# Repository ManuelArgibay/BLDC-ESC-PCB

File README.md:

# Controlador de motor BLDC (ESC sensorless) — PCB en KiCad

Placa de potencia y acondicionamiento para controlar un motor BLDC trifásico sin sensores Hall desde una LaunchPad **TI Tiva C TM4C123GXL**. Integra el inversor trifásico con sus drivers, la detección de cruces por cero de la fuerza contraelectromotriz (BEMF) para conmutación sensorless y la alimentación de toda la placa a partir de una única entrada de 12 V.

Proyecto de la asignatura *Laboratori de Sistemes Electrònics I* (Grado en Ingeniería Electrónica de Telecomunicación, Universitat de Barcelona).

## Características

| | |
|---|---|
| Herramienta | KiCad 9 |
| Dimensiones | 70 × 90 mm, 2 taladros M3 |
| Capas | 4 (F.Cu, In1.Cu, In2.Cu, B.Cu), 1,57 mm |
| Alimentación | 12 V (bus del motor y lógica) |
| Etapa de potencia | 6 × MOSFET canal N en DPAK (TO-252), tres semipuentes |
| Drivers | 3 × IR2301 (high/low side con bootstrap) |
| Detección BEMF | LM339 (comparador cuádruple) + neutro virtual resistivo |
| Reguladores | AP1509-50 (buck 12 V → 5 V) + LMS8117 (LDO 5 V → 3,3 V) |
| Controlador | Tiva C TM4C123GXL (se monta sobre los conectores J1–J4) |

## Descripción del circuito

El esquema es jerárquico. La hoja raíz agrupa cuatro bloques: **TM4C123GXL** (conectores de la LaunchPad), **Motor** (que contiene las subhojas *Drivers* y *Comparadores*), **IO** (alimentación, conectores y LEDs) y **Testpoints**.

**Etapa de potencia (`Drivers.kicad_sch`).** Cada fase es un semipuente de dos NMOS (MxH/MxL) alimentado desde el bus de 12 V. Un IR2301 por fase genera las tensiones de puerta: el lado alto se alimenta por bootstrap (diodo 1N4149 + condensador entre VB y la fase), cada puerta tiene su resistencia serie (RGxH/RGxL) y cada entrada lógica una resistencia (RIxH/RIxL) desde la Tiva. Las entradas de lado alto van a pines con salida PWM y las de lado bajo a GPIO.

**Detección de BEMF (`Comparadores.kicad_sch`).** Tres resistencias en estrella (RFA/RFB/RFC) reconstruyen el neutro virtual del motor. La tensión de cada fase y la del neutro pasan por divisores resistivos que las llevan a un rango compatible con la lógica de 3,3 V, y un LM339 compara cada fase flotante contra el neutro. Las salidas en colector abierto tienen pull-up a 3,3 V y entran a la Tiva como señales digitales de cruce por cero, que el firmware usa para temporizar la conmutación.

**Alimentación e IO (`IO.kicad_sch`).** La entrada de 12 V (bornera) alimenta directamente el bus de potencia y los drivers. Un buck AP1509-50 (bobina de 47 µH, diodo Schottky B220) genera 5 V y un LDO LMS8117 baja a 3,3 V. Dos jumpers permiten elegir de dónde sale el raíl de 3,3 V de la placa: del LDO (`FUENTE`) y/o del regulador de la propia Tiva (`TIVA`). Hay un LED indicador de 12 V y otro del 3,3 V de la Tiva, y una bornera de tres vías para las fases del motor.

**Test points (`Testpoints.kicad_sch`).** Acceso a las entradas lógicas de los drivers, las puertas de los seis MOSFET, los nodos de bootstrap, las tres fases, VCC, 3,3 V y el potenciómetro, pensado para depurar la placa con osciloscopio.

## Asignación de pines (TM4C123GXL)

| Señal | Pin Tiva | Función |
|---|---|---|
| Fase A alto / bajo | PB5 / PD0 | Entradas HIN / LIN del IR2301 A |
| Fase B alto / bajo | PD1 / PB3 | Entradas HIN / LIN del IR2301 B |
| Fase C alto / bajo | PB7 / PF2 | Entradas HIN / LIN del IR2301 C |
| BEMF A / B / C | PD2 / PD3 / PD6 | Salidas del LM339 |
| Potenciómetro | PE0 (AIN3) | Consigna analógica de velocidad |
| SPI | PA2 (SCLK), PA5 (MOSI), PA4 (MISO), PF1 (SS) | Conector de expansión |

## Estructura del repositorio

```
Control Motor BLDC.kicad_pro   Proyecto de KiCad
Control Motor BLDC.kicad_sch   Hoja raíz del esquema
Control Motor BLDC.kicad_pcb   Layout
*.kicad_sch                    Subhojas (Drivers, Comparadores, IO, Motor, TM4C123GXL, Testpoints)
Footprints/                    Símbolos y footprints propios (NMOS DPAK, AP1509, LDO)
LSE-BLDC_control/              Firmware para la Tiva (Code Composer Studio, C bare-metal)
docs/                          Imágenes del README
```

Las librerías propias se referencian con `${KIPRJMOD}` en `fp-lib-table` y `sym-lib-table`, así que el proyecto abre sin configuración adicional en KiCad 9 o posterior.

## Autor

Manuel Argibay Molina y Max Pérez Piqué — [@ManuelArgibay](https://github.com/ManuelArgibay)

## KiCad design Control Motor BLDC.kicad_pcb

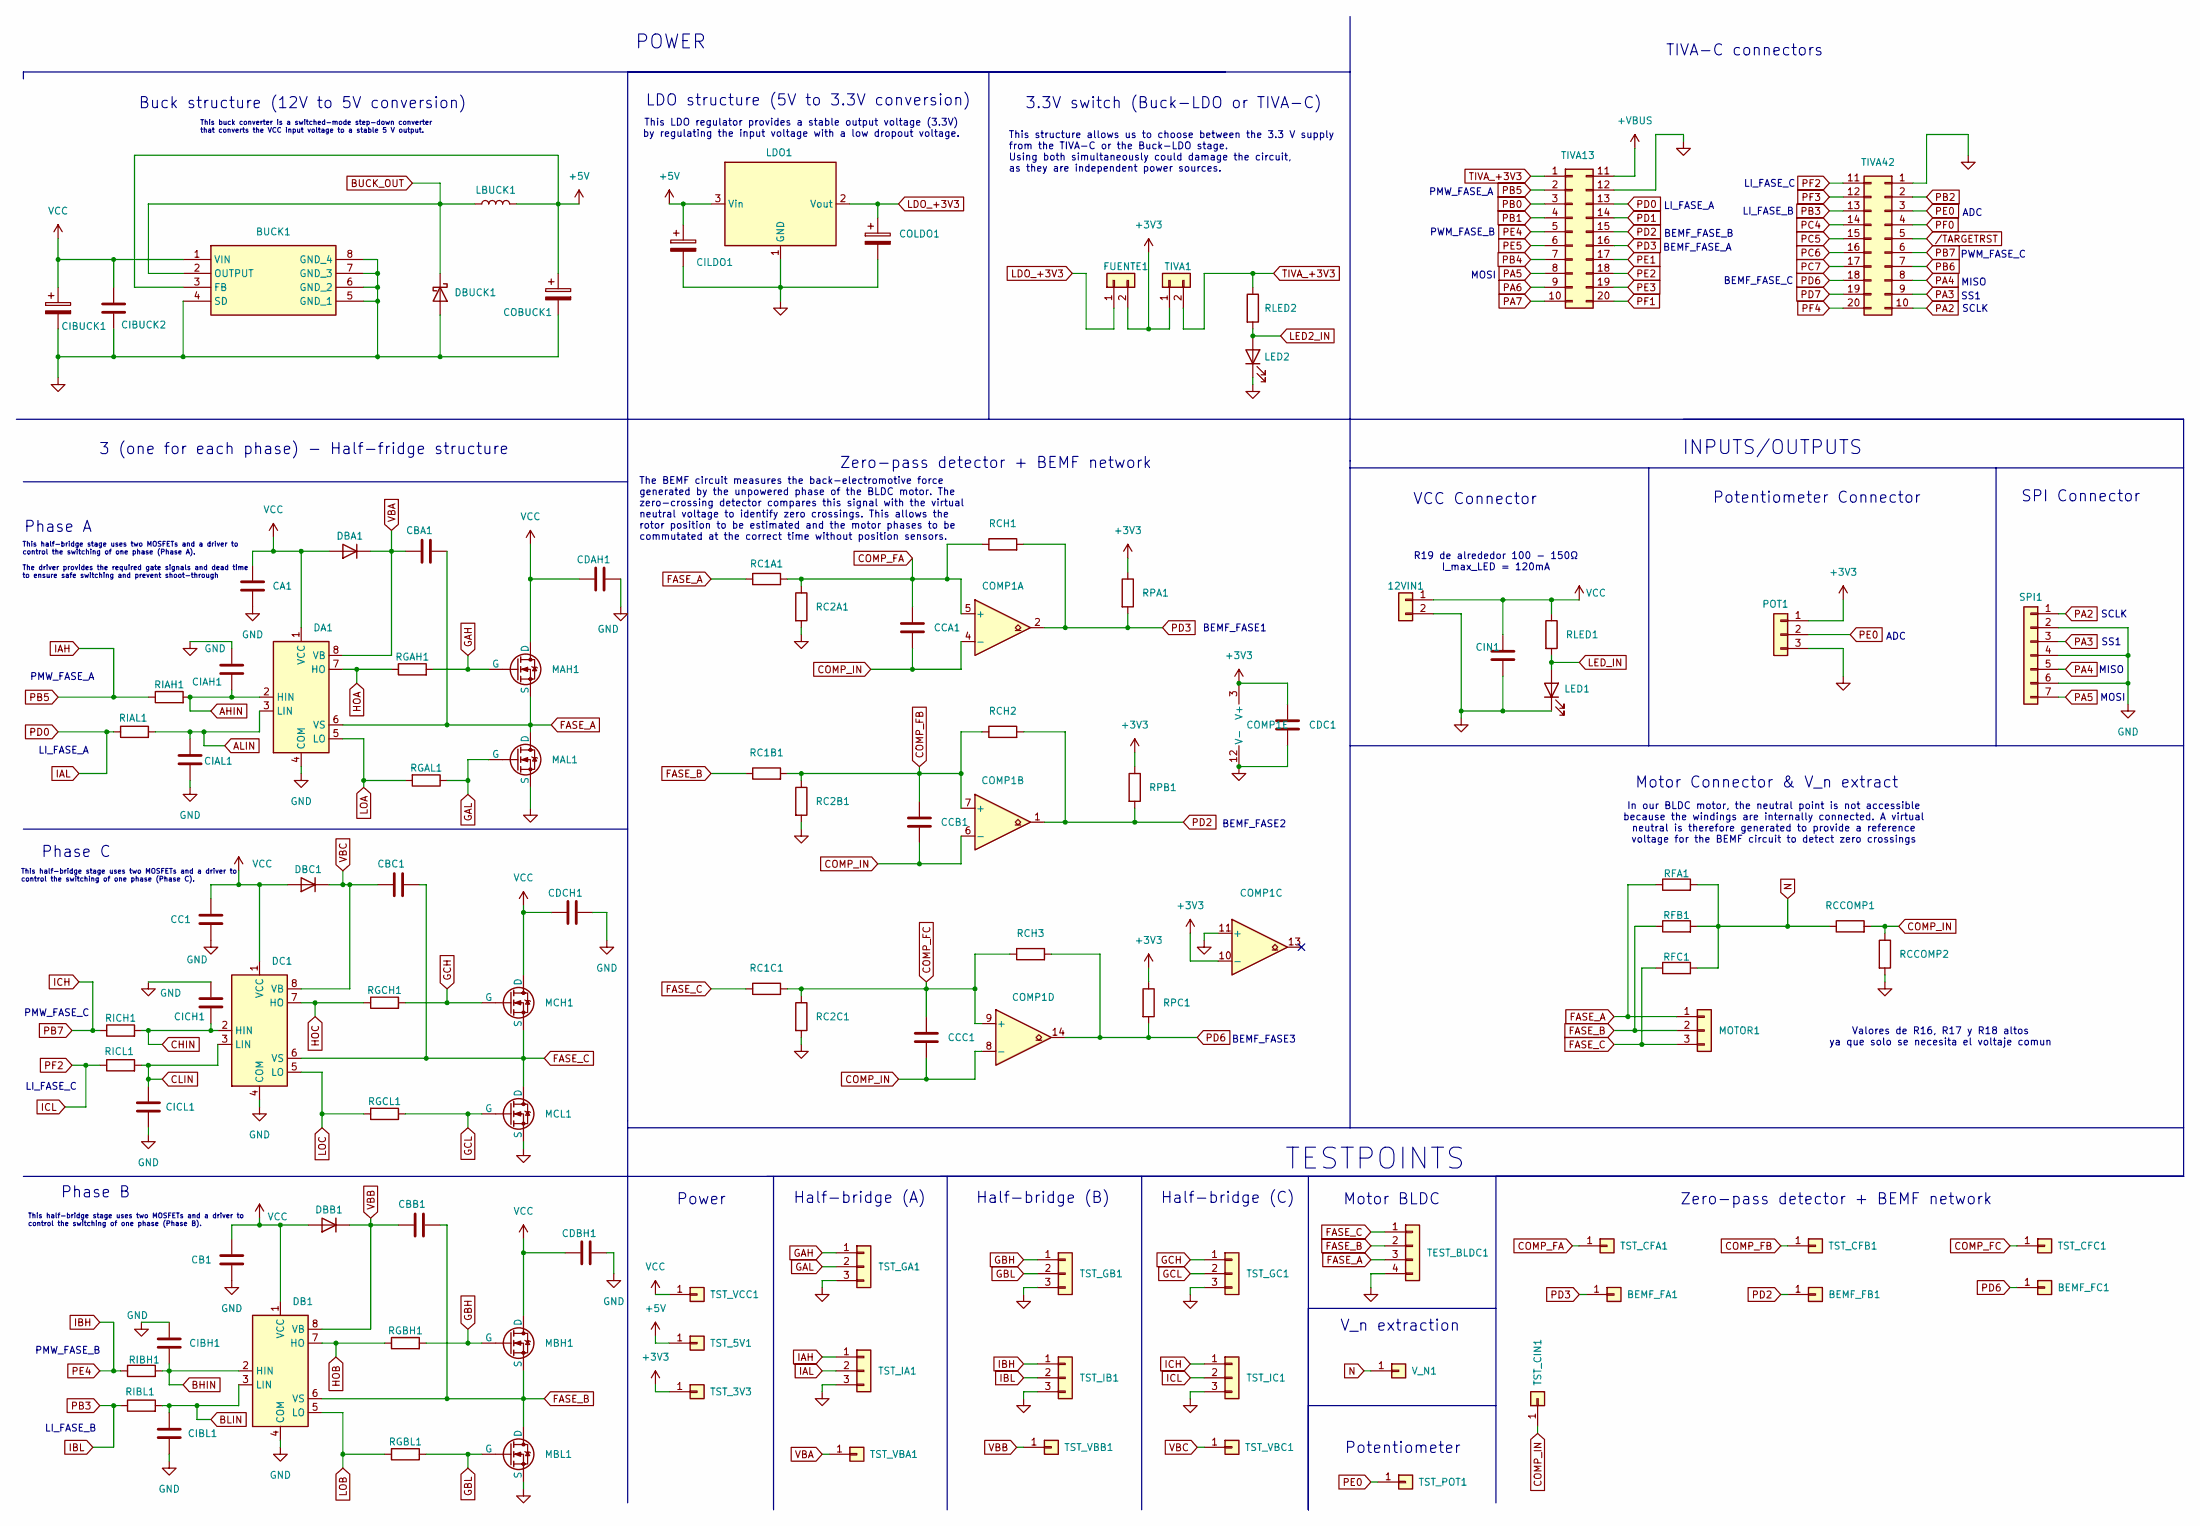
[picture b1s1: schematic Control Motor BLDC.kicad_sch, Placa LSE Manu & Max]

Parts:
12VIN1: Conn_01x02; TerminalBlock_Phoenix_MKDS-1,5-2-5.08_1x02_P5.08mm_Horizont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
BEMF_FA1: Conn_01x01; PinSocket_1x01_P2.54mm_Vertical
BEMF_FB1: Conn_01x01; PinSocket_1x01_P2.54mm_Vertical
BEMF_FC1: Conn_01x01; PinSocket_1x01_P2.54mm_Vertical
BUCK1: AP1509-50SG-13; SOP-8_3.76x4.96mm_P1.27mm; Mouser Part Number 621-AP1509-50SG-13
CA1: C; C_1206_3216Metric
CB1: C; C_1206_3216Metric
CBA1: C; C_1206_3216Metric
CBB1: C; C_1206_3216Metric
CBC1: C; C_1206_3216Metric
CC1: C; C_1206_3216Metric
CCA1: C; C_1206_3216Metric
CCB1: C; C_1206_3216Metric
CCC1: C; C_1206_3216Metric
CDAH1: C; C_1206_3216Metric
CDBH1: C; C_1206_3216Metric
CDC1: C; C_1206_3216Metric
CDCH1: C; C_1206_3216Metric
CIAH1: C; C_1206_3216Metric
CIAL1: C; C_1206_3216Metric
CIBH1: C; C_1206_3216Metric
CIBL1: C; C_1206_3216Metric
CIBUCK1: C_Polarized; CP_Elec_8x6.2
CIBUCK2: C; C_1206_3216Metric
CICH1: C; C_1206_3216Metric
CICL1: C; C_1206_3216Metric
CILDO1: C_Polarized; C_1206_3216Metric
CIN1: C; CP_Elec_8x6.2
COBUCK1: C_Polarized; CP_Elec_8x6.2
COLDO1: C_Polarized; C_1206_3216Metric
COMP1: LM339; SOIC-14_3.9x8.7mm_P1.27mm
DA1: IR2301; SOIC-8_3.9x4.9mm_P1.27mm
DB1: IR2301; SOIC-8_3.9x4.9mm_P1.27mm
DBA1: 1N4149; D_DO-35_SOD27_P7.62mm_Horizontal
DBB1: 1N4149; D_DO-35_SOD27_P7.62mm_Horizontal
DBC1: 1N4149; D_DO-35_SOD27_P7.62mm_Horizontal
DBUCK1: B220; D_SMB
DC1: IR2301; SOIC-8_3.9x4.9mm_P1.27mm
FUENTE1: Conn_01x02; PinHeader_1x02_P2.54mm_Vertical
LBUCK1: 47µH; Inductor
LDO1: LMS8117; SOT-223-3_TabPin2
LED1, LED2: LED; LED_D3.0mm
MAH1: NMOS
MAL1: NMOS
MBH1: NMOS
MBL1: NMOS
MCH1: NMOS
MCL1: NMOS
MOTOR1: Conn_01x03; TerminalBlock_Phoenix_MKDS-1,5-3-5.08_1x03_P5.08mm_Horizont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
POT1: Conn_01x03; TerminalBlock_Phoenix_MKDS-1,5-3-5.08_1x03_P5.08mm_Horizont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
RC1A1, RC1B1, RC1C1, RC2A1, RC2B1, RC2C1: R; R_1206_3216Metric
RCCOMP1, RCCOMP2: R; R_1206_3216Metric
RCH1, RCH2, RCH3: R; R_1206_3216Metric
RFA1: R; R_1206_3216Metric
RFB1: R; R_1206_3216Metric
RFC1: R; R_1206_3216Metric
RGAH1: R; R_1206_3216Metric
RGAL1: R; R_1206_3216Metric
RGBH1: R; R_1206_3216Metric
RGBL1: R; R_1206_3216Metric
RGCH1: R; R_1206_3216Metric
RGCL1: R; R_1206_3216Metric
RIAH1: R; R_1206_3216Metric
RIAL1: R; R_1206_3216Metric
RIBH1: R; R_1206_3216Metric
RIBL1: R; R_1206_3216Metric
RICH1: R; R_1206_3216Metric
RICL1: R; R_1206_3216Metric
RLED1, RLED2: R; R_1206_3216Metric
RPA1: R; R_1206_3216Metric
RPB1: R; R_1206_3216Metric
RPC1: R; R_1206_3216Metric
SPI1: Conn_01x07; PinHeader_1x07_P2.54mm_Vertical
TEST_BLDC1: Conn_01x04; PinHeader_1x04_P2.54mm_Vertical
TIVA1: Conn_01x02; PinHeader_1x02_P2.54mm_Vertical
TIVA13, TIVA42: Conn_02x10_Top_Bottom; PinSocket_2x10_P2.54mm_Vertical
TST_3V3, TST_5V1: Conn_01x01; PinSocket_1x01_P2.54mm_Vertical
TST_CFA1: Conn_01x01; PinSocket_1x01_P2.54mm_Vertical
TST_CFB1: Conn_01x01; PinSocket_1x01_P2.54mm_Vertical
TST_CFC1: Conn_01x01; PinSocket_1x01_P2.54mm_Vertical
TST_CIN1: Conn_01x01; PinSocket_1x01_P2.54mm_Vertical
TST_GA1: Conn_01x03; PinSocket_1x03_P2.54mm_Vertical
TST_GB1: Conn_01x03; PinSocket_1x03_P2.54mm_Vertical
TST_GC1: Conn_01x03; PinSocket_1x03_P2.54mm_Vertical
TST_IA1: Conn_01x03; PinSocket_1x03_P2.54mm_Vertical
TST_IB1: Conn_01x03; PinSocket_1x03_P2.54mm_Vertical
TST_IC1: Conn_01x03; PinSocket_1x03_P2.54mm_Vertical
TST_POT1: Conn_01x01; PinSocket_1x01_P2.54mm_Vertical
TST_VBA1: Conn_01x01; PinSocket_1x01_P2.54mm_Vertical
TST_VBB1: Conn_01x01; PinSocket_1x01_P2.54mm_Vertical
TST_VBC1: Conn_01x01; PinSocket_1x01_P2.54mm_Vertical
TST_VCC1: Conn_01x01; PinSocket_1x01_P2.54mm_Vertical
V_N1: Conn_01x01; PinSocket_1x01_P2.54mm_Vertical

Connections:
+3V3: CDC1.1, COMP1.3 (V+), COMP1.10 (-), FUENTE1.2, POT1.1, RPA1.1, RPB1.1, RPC1.1, TIVA1.1, TST_3V3.1
+5V: BUCK1.3 (FB), CILDO1.1, COBUCK1.1, LBUCK1.2, LDO1.3 (Vin), TST_5V1.1
+VBUS: TIVA13.11
AHIN: CIAH1.2, DA1.2 (HIN), RIAH1.2
ALIN: CIAL1.2, DA1.3 (LIN), RIAL1.2
BHIN: CIBH1.2, DB1.2 (HIN), RIBH1.2
BLIN: CIBL1.2, DB1.3 (LIN), RIBL1.2
BUCK_OUT: BUCK1.2 (OUTPUT), DBUCK1.1 (K), LBUCK1.1
CHIN: CICH1.2, DC1.2 (HIN), RICH1.2
CLIN: CICL1.2, DC1.3 (LIN), RICL1.2
COMP_FA: CCA1.1, COMP1.5 (+), RC1A1.2, RC2A1.1, RCH1.1, TST_CFA1.1
COMP_FB: CCB1.1, COMP1.7 (+), RC1B1.2, RC2B1.1, RCH2.1, TST_CFB1.1
COMP_FC: CCC1.1, COMP1.9 (+), RC1C1.2, RC2C1.1, RCH3.1, TST_CFC1.1
COMP_IN: CCA1.2, CCB1.2, CCC1.2, COMP1.4 (-), COMP1.6 (-), COMP1.8 (-), RCCOMP1.2, RCCOMP2.1, TST_CIN1.1
FASE_A: CBA1.2, DA1.6 (VS), MAH1.3 (S), MAL1.1 (D), MOTOR1.1, RC1A1.1, RFA1.1, TEST_BLDC1.3
FASE_B: CBB1.2, DB1.6 (VS), MBH1.3 (S), MBL1.1 (D), MOTOR1.2, RC1B1.1, RFB1.1, TEST_BLDC1.2
FASE_C: CBC1.2, DC1.6 (VS), MCH1.3 (S), MCL1.1 (D), MOTOR1.3, RC1C1.1, RFC1.1, TEST_BLDC1.1
GAH: MAH1.2 (G), RGAH1.2, TST_GA1.1
GAL: MAL1.2 (G), RGAL1.1, TST_GA1.2
GBH: MBH1.2 (G), RGBH1.2, TST_GB1.1
GBL: MBL1.2 (G), RGBL1.1, TST_GB1.2
GCH: MCH1.2 (G), RGCH1.2, TST_GC1.1
GCL: MCL1.2 (G), RGCL1.1, TST_GC1.2
GND: 12VIN1.2, BUCK1.4 (SD), BUCK1.5 (GND_1), BUCK1.6 (GND_2), BUCK1.7 (GND_3), BUCK1.8 (GND_4), CA1.2, CB1.1, CC1.1, CDAH1.2, CDBH1.2, CDC1.2, CDCH1.2, CIAH1.1, CIAL1.1, CIBH1.1, CIBL1.1, CIBUCK1.2, CIBUCK2.2, CICH1.1, CICL1.1, CILDO1.2, CIN1.2, COBUCK1.2, COLDO1.2, COMP1.11 (+), COMP1.12 (V-), DA1.4 (COM), DB1.4 (COM), DBUCK1.2 (A), DC1.4 (COM), LDO1.1 (GND), LED1.1 (K), LED2.1 (K), MAL1.3 (S), MBL1.3 (S), MCL1.3 (S), POT1.3, RC2A1.2, RC2B1.2, RC2C1.2, RCCOMP2.2, SPI1.2, SPI1.4, SPI1.6, TEST_BLDC1.4, TIVA13.12, TIVA42.1, TST_GA1.3, TST_GB1.3, TST_GC1.3, TST_IA1.3, TST_IB1.3, TST_IC1.3
HOA: DA1.7 (HO), RGAH1.1
HOB: DB1.7 (HO), RGBH1.1
HOC: DC1.7 (HO), RGCH1.1
IAH: RIAH1.1, TIVA13.2, TST_IA1.1
IAL: RIAL1.1, TIVA13.13, TST_IA1.2
IBH: RIBH1.1, TIVA13.5, TST_IB1.1
IBL: RIBL1.1, TIVA42.13, TST_IB1.2
ICH: RICH1.1, TIVA42.6, TST_IC1.1
ICL: RICL1.1, TIVA42.11, TST_IC1.2
LDO_+3V3: COLDO1.1, FUENTE1.1, LDO1.2 (Vout)
LED2_IN: LED2.2 (A), RLED2.2
LED_IN: LED1.2 (A), RLED1.2
LOA: DA1.5 (LO), RGAL1.2
LOB: DB1.5 (LO), RGBL1.2
LOC: DC1.5 (LO), RGCL1.2
N: RCCOMP1.1, RFA1.2, RFB1.2, RFC1.2, V_N1.1
PA2: SPI1.1, TIVA42.10
PA3: SPI1.3, TIVA42.9
PA4: SPI1.5, TIVA42.8
PA5: SPI1.7, TIVA13.8
PA6: TIVA13.9
PA7: TIVA13.10
PB0: TIVA13.3
PB1: TIVA13.4
PB2: TIVA42.2
PB4: TIVA13.7
PB6: TIVA42.7
PC4: TIVA42.14
PC5: TIVA42.15
PC6: TIVA42.16
PC7: TIVA42.17
PD1: TIVA13.14
PD2: BEMF_FB1.1, COMP1.1, RCH2.2, RPB1.2, TIVA13.15
PD3: BEMF_FA1.1, COMP1.2, RCH1.2, RPA1.2, TIVA13.16
PD6: BEMF_FC1.1, COMP1.14, RCH3.2, RPC1.2, TIVA42.18
PD7: TIVA42.19
PE0: POT1.2, TIVA42.3, TST_POT1.1
PE1: TIVA13.17
PE2: TIVA13.18
PE3: TIVA13.19
PE5: TIVA13.6
PF0: TIVA42.4
PF1: TIVA13.20
PF3: TIVA42.12
PF4: TIVA42.20
TIVA_+3V3: RLED2.1, TIVA1.2, TIVA13.1
VBA: CBA1.1, DA1.8 (VB), DBA1.1 (K), TST_VBA1.1
VBB: CBB1.1, DB1.8 (VB), DBB1.1 (K), TST_VBB1.1
VBC: CBC1.1, DBC1.1 (K), DC1.8 (VB), TST_VBC1.1
VCC: 12VIN1.1, BUCK1.1 (VIN), CA1.1, CB1.2, CC1.2, CDAH1.1, CDBH1.1, CDCH1.1, CIBUCK1.1, CIBUCK2.1, CIN1.1, DA1.1 (VCC), DB1.1 (VCC), DBA1.2 (A), DBB1.2 (A), DBC1.2 (A), DC1.1 (VCC), MAH1.1 (D), MBH1.1 (D), MCH1.1 (D), RLED1.1, TST_VCC1.1; also elsewhere on the board
/TARGETRST: TIVA42.5

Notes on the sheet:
Buck structure (12V to 5V conversion)
Half-bridge (A)
Phase C
Potentiometer Connector
LI_FASE_A
Phase A
Half-bridge (B)
SS1
PMW_FASE_A
PMW_FASE_C
Phase B
ADC
SPI Connector
The BEMF circuit measures the back-electromotive force generated by the unpowered phase of the BLDC motor. The zero-crossing detector compares this signal with the virtual neutral voltage to identify zero crossings. This allows the rotor position to be estimated and the motor phases to be commutate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
This half-bridge stage uses two MOSFETs and a driver to control the switching of one phase (Phase C).
Power
This structure allows us to choose between the 3.3 V supply from the TIVA-C or the Buck-LDO stage. Using both simultaneously could damage the circuit, as they are independent power sources.
MISO
Valores de R16, R17 y R18 altos ya que solo se necesita el voltaje comun
TESTPOINTS
SCLK
TIVA-C connectors
3.3V switch (Buck-LDO or TIVA-C)
BEMF_FASE_A
MOSI
VCC Connector
PWM_FASE_B
This half-bridge stage uses two MOSFETs and a driver to control the switching of one phase (Phase A). The driver provides the required gate signals and dead time to ensure safe switching and prevent shoot-through
BEMF_FASE2
Potentiometer
PWM_FASE_C
R19 de alrededor 100 - 150Ω I_max_LED = 120mA
3 (one for each phase) - Half-fridge structure
LI_FASE_C
BEMF_FASE_C
Motor Connector & V_n extract
This buck converter is a switched-mode step-down converter that converts the VCC input voltage to a stable 5 V output.
This half-bridge stage uses two MOSFETs and a driver to control the switching of one phase (Phase B).
LI_FASE_B
POWER

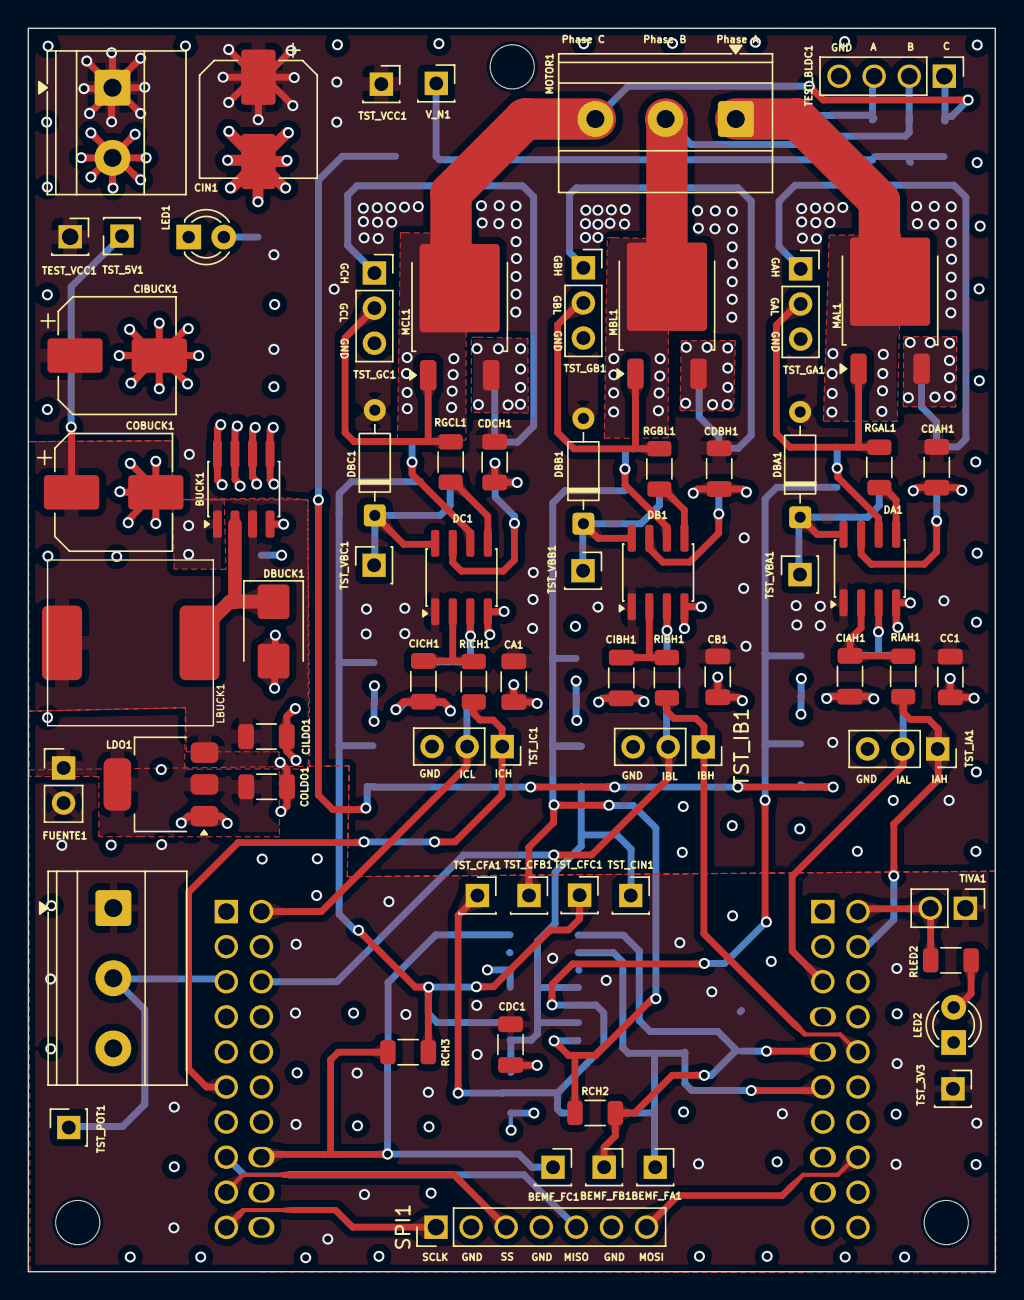
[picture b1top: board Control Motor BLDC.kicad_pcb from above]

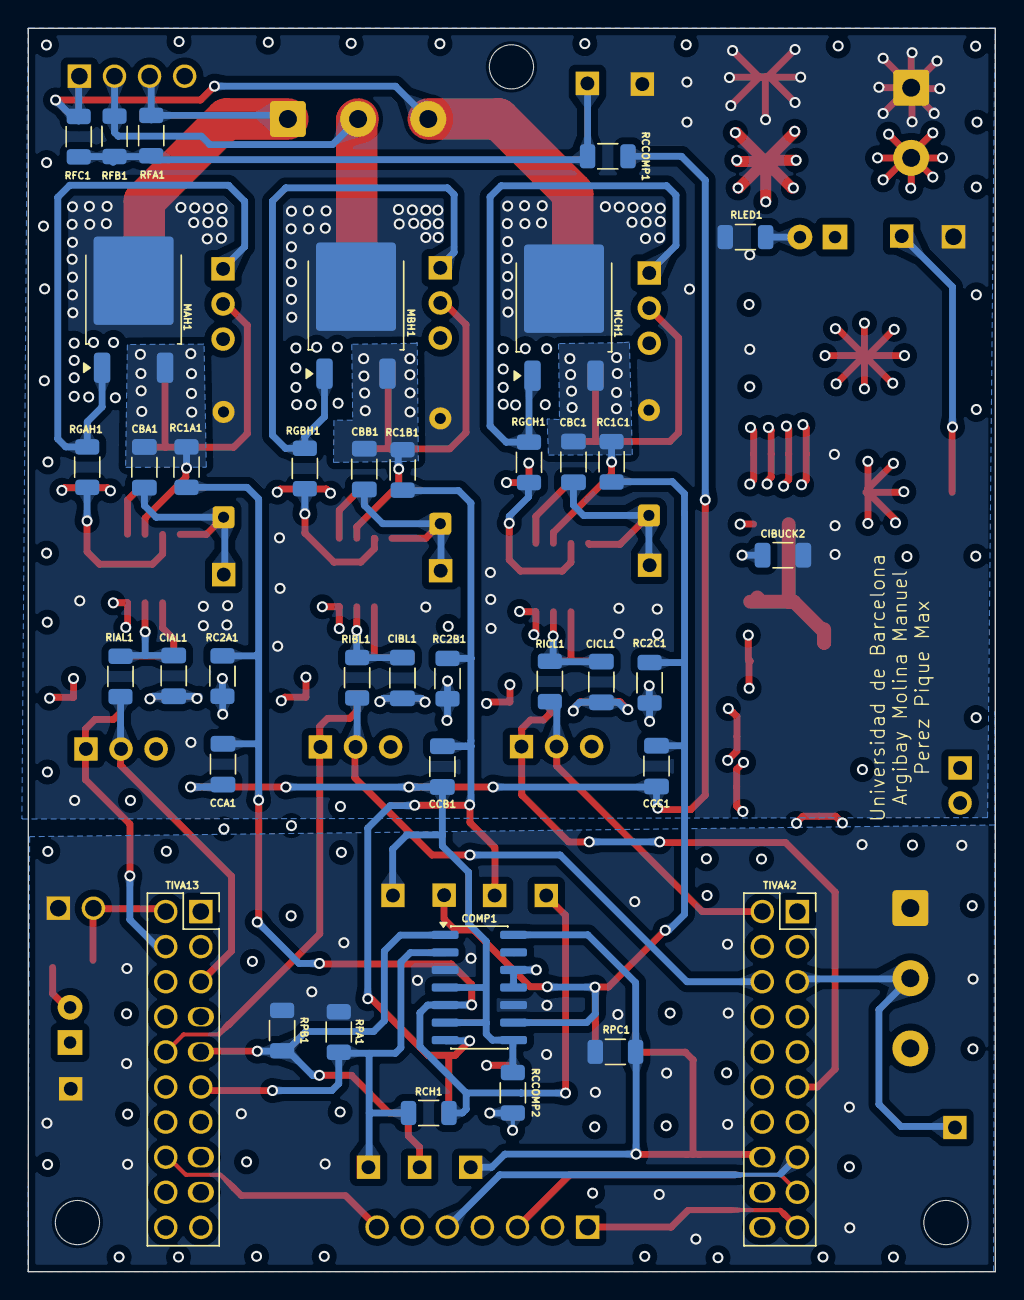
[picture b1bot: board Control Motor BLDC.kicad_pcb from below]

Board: 4 copper layers, 70.0 x 90.0 mm, 106 parts (38 on the bottom side), 52 nets.

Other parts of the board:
TEST_VCC1: Conn_01x01; PinSocket_1x01_P2.54mm_Vertical

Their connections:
VCC: TEST_VCC1.1; also elsewhere on the board
